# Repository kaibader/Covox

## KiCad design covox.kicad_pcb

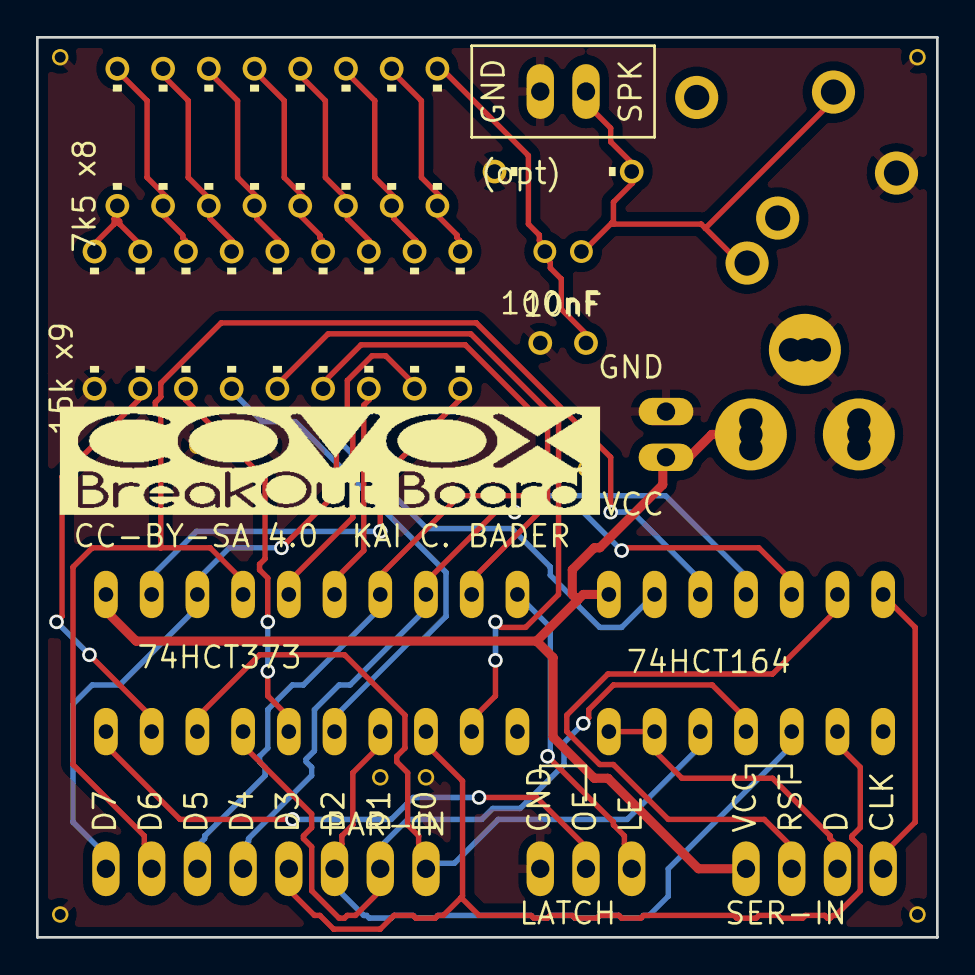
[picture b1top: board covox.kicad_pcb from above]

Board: 2 copper layers, 50.0 x 50.0 mm, 41 parts (0 on the bottom side), 33 nets.

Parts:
C1: 100nF; E2-4
C2: 10nF; C025-025X050
CN1: POWERJACK; POWERJACK_SLOT
IC1: 74HCT164; DIL14
IC2: 74HCT373; DIL20
JP1: PAR-IN; 1X08
JP2: LATCH; 1X03
JP3: SER-IN; 1X04
JP4: PWR; 1X02
JP5: AUDIO; AUDIO-JACK-3.5MM
JP6: AUDIO; 1X02
R1, R2, R3, R4, R5, R6, R7, R8, R9: 15k; 0204%2f7
R10, R11, R12, R13, R14, R15, R16, R17: 7k5; 0204%2f7
R18: 47k (optional); 0204%2f7
U$2: COVOX_LOGO_600
VP_0, VP_1, VP_2, VP_3, VP_4, VP_5, VP_6, VP_7, VP_8, VP_9, VP_10: VPDEV0; VPAC0

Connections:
/AOUT: C1.+, C2.1, R17.2
/N$1: R1.2, R2.2, R10.1
/N$2: R3.2, R10.2, R11.1
/N$3: R4.2, R11.2, R12.1
/N$4: R5.2, R12.2, R13.1
/N$5: R6.2, R13.2, R14.1
/N$6: R7.2, R14.2, R15.1
/N$7: R8.2, R15.2, R16.1
/N$8: IC2.2, R2.1
/N$9: IC2.5, R3.1
/N$10: IC2.6, R4.1
/N$11: IC2.9, R5.1
/N$12: IC2.12, R6.1
/N$13: IC2.15, R7.1
/N$14: IC2.16, R8.1
/N$15: IC2.19, R9.1
/N$16: IC1.1, IC1.2, JP3.3
/N$17: R9.2, R16.2, R17.1
/N$18: IC1.3, IC2.3, JP1.1
/N$19: IC1.4, IC2.4, JP1.2
/N$20: IC1.5, IC2.7, JP1.3
/N$21: IC1.6, IC2.8, JP1.4
/N$22: IC1.10, IC2.13, JP1.5
/N$23: IC1.11, IC2.14, JP1.6
/N$24: IC1.12, IC2.17, JP1.7
/N$25: IC1.13, IC2.18, JP1.8
/N$26: IC2.1, JP2.2
/N$27: IC2.11, JP2.3
/N$30: IC1.9, JP3.2
/N$31: IC1.8, JP3.4
/N$32: C1.-, JP5.2, JP5.3, JP6.1, R18.2
GND: C2.2, CN1.GND@, CN1.GNDB, JP2.1, JP4.2, JP5.1, JP6.2, R1.1, R18.1, VP_0.VP, VP_1.VP, VP_2.VP, VP_3.VP, VP_4.VP, VP_5.VP, VP_6.VP, VP_7.VP, VP_8.VP, VP_9.VP, VP_10.VP
VCC: CN1.PWR@, JP3.1, JP4.1

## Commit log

2015-05-20 Initial commit. Work in progress...
2015-05-20 Updates...
2015-05-25 Generated Covox Gerber files.
2017-06-10 Ported design files from EagleCAD to KiCad.
    This was a test of the Eagle-to-KiCad toolset to port a whole project from
    EagleCAD to KiCad. The resulting board file is currently broken due to
    copper fill settings between the two design tools.
2017-06-10 Moved EagleCAD files into a separate directory

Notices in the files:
covox.kicad_pcb:
CC-BY-SA 4.0  KAI C. BADER
